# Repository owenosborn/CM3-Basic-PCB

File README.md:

# CM3-Basic-PCB

A basic PCB layout for the Raspberry Pi Compute Module 3 in Eagle.

Uses most of the same parts as the CMIO board.

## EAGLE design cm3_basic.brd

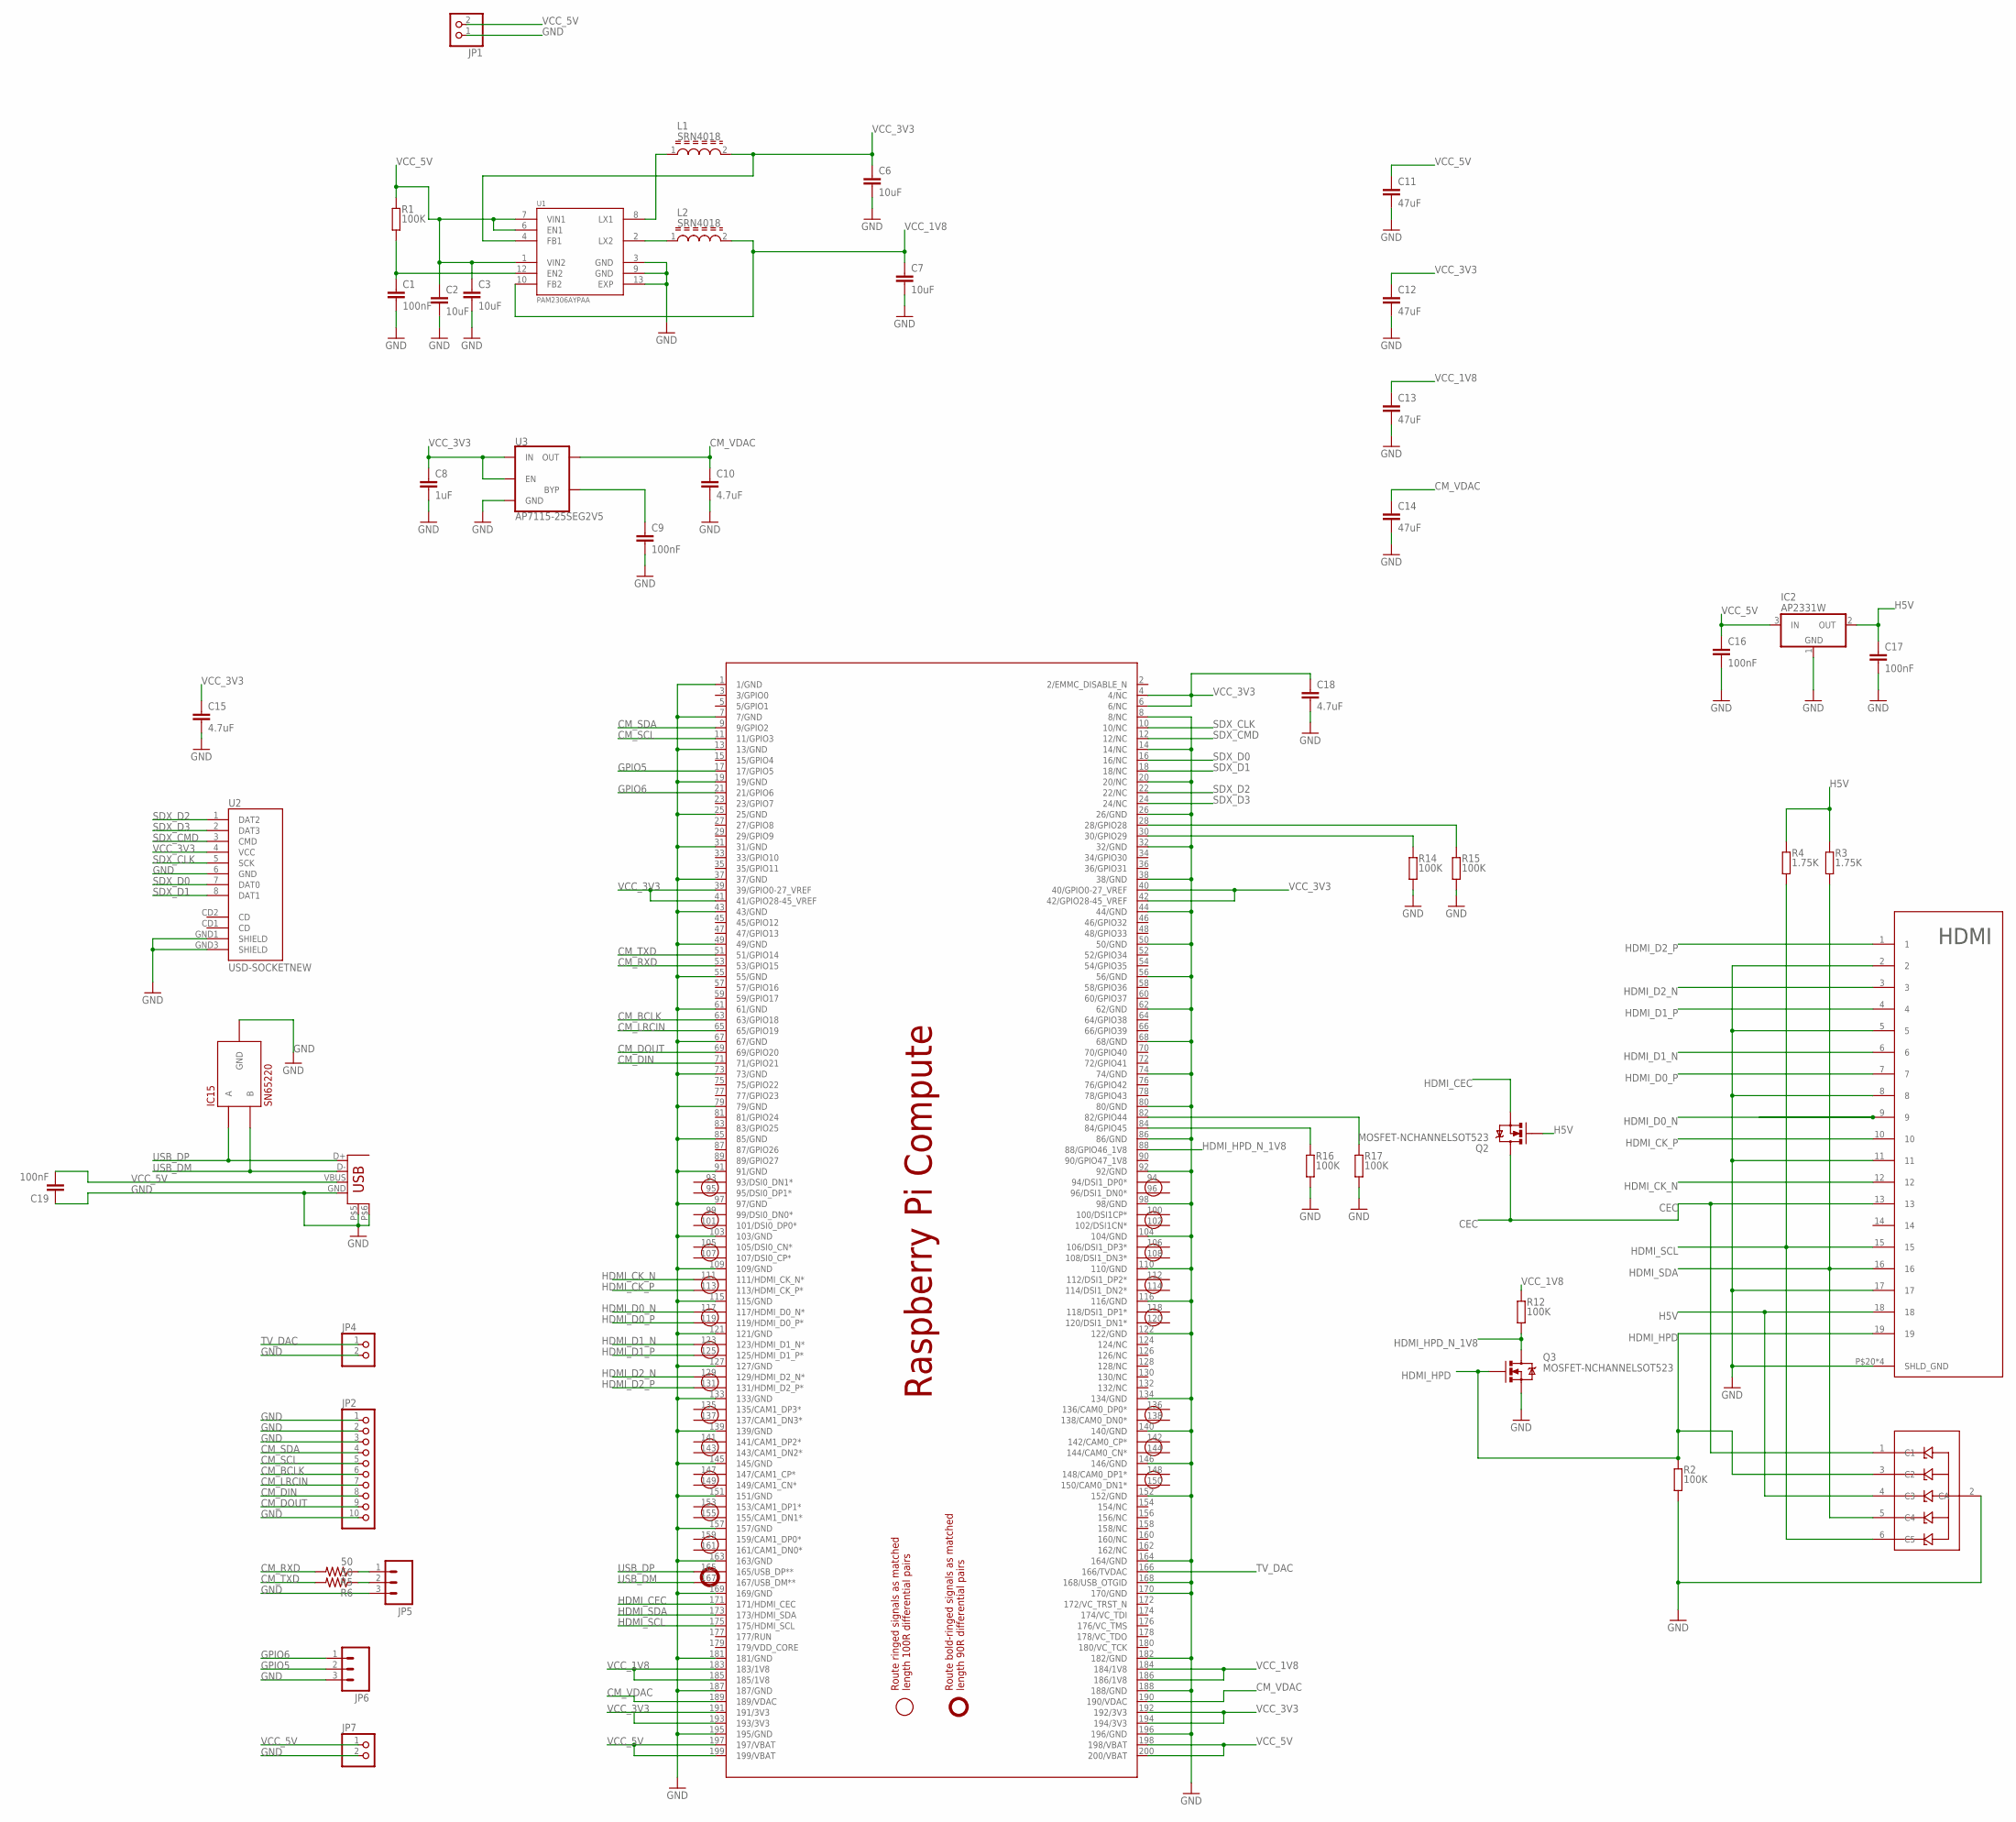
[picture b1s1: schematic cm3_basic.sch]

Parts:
C1, C9, C16, C17: 100nF; C0603
C2, C3, C6, C7: 10uF; C0805
C8: 1uF; C0603
C10, C15: 4.7uF; C0603
C11, C12, C13, C14: 47uF; C3216
C18: 4.7uF; C1608
C19: 100nF; 0603-CAP
IC1: PESD3V3L5UYSOT363; SOT363-INFINION
IC2: AP2331W; SOT23
IC15: SN65220; SOT23-6L
JP1, JP4, JP7: PINHD-1X2; 1X02
JP2: PINHD-1X10; 1X10
JP3: USB-A; USB-A-S-NOSILK-FEMALE
JP5, JP6: M03LOCK_LONGPADS; 1X03_LOCK_LONGPADS
L1, L2: SRN4018; INDP4040X180N
Q2, Q3: MOSFET-NCHANNELSOT523; SOT523
R1, R2, R12, R14, R15, R16, R17: 100K; R0603
R3, R4: 1.75K; R0603
R5, R6: 50; 0603-RES
SODIMM: RPI_COMPUTE
U1: PAM2306AYPAA; SON45P300X300X80-13N
U2: USD-SOCKETNEW; MICRO-SD-SOCKET-PP
U3: AP7115-25SEG2V5; SC70
U4: HDMI

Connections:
CEC: IC1.1 (C1), Q2.3 (D), U4.13
CM_BCLK: JP2.6, SODIMM.63 (63/GPIO18)
CM_DIN: JP2.8, SODIMM.71 (71/GPIO21)
CM_DOUT: JP2.9, SODIMM.69 (69/GPIO20)
CM_LRCIN: JP2.7, SODIMM.65 (65/GPIO19)
CM_RXD: R5.2, SODIMM.53 (53/GPIO15)
CM_SCL: JP2.5, SODIMM.11 (11/GPIO3)
CM_SDA: JP2.4, SODIMM.9 (9/GPIO2)
CM_TXD: R6.2, SODIMM.51 (51/GPIO14)
CM_VDAC: C10.1, C14.1, SODIMM.189 (189/VDAC), SODIMM.190 (190/VDAC), U3.5 (OUT)
GND: C1.2, C2.2, C3.2, C6.2, C7.2, C8.2, C9.2, C10.2, C11.2, C12.2, C13.2, C14.2, C15.2, C16.2, C17.2, C18.2, C19.1, IC1.2 (CA), IC2.1 (GND), IC15.2 (GND), IC15.5 (GND), JP1.1, JP2.1, JP2.2, JP2.3, JP2.10, JP3.GND, JP3.P$5 (SHIELD1), JP3.P$6 (SHIELD2), JP4.2, JP5.3, JP6.3, JP7.2, Q3.2 (S), R2.1, R14.1, R15.1, R16.1, R17.1, SODIMM.1 (1/GND), SODIMM.7 (7/GND), SODIMM.8 (8/NC), SODIMM.13 (13/GND), SODIMM.14 (14/NC), SODIMM.19 (19/GND), SODIMM.20 (20/NC), SODIMM.25 (25/GND), SODIMM.26 (26/GND), SODIMM.31 (31/GND), SODIMM.32 (32/GND), SODIMM.37 (37/GND), SODIMM.38 (38/GND), SODIMM.43 (43/GND), SODIMM.44 (44/GND), SODIMM.49 (49/GND), SODIMM.50 (50/GND), SODIMM.55 (55/GND), SODIMM.56 (56/GND), SODIMM.61 (61/GND), SODIMM.62 (62/GND), SODIMM.67 (67/GND), SODIMM.68 (68/GND), SODIMM.73 (73/GND), SODIMM.74 (74/GND), SODIMM.79 (79/GND), SODIMM.80 (80/GND), SODIMM.85 (85/GND), SODIMM.86 (86/GND), SODIMM.91 (91/GND), SODIMM.92 (92/GND), SODIMM.97 (97/GND), SODIMM.98 (98/GND), SODIMM.103 (103/GND), SODIMM.104 (104/GND), SODIMM.109 (109/GND), SODIMM.110 (110/GND), SODIMM.115 (115/GND), SODIMM.116 (116/GND), SODIMM.121 (121/GND), SODIMM.122 (122/GND), SODIMM.127 (127/GND), SODIMM.133 (133/GND), SODIMM.134 (134/GND), SODIMM.139 (139/GND), SODIMM.140 (140/GND), SODIMM.145 (145/GND), SODIMM.146 (146/GND), SODIMM.151 (151/GND), SODIMM.152 (152/GND), SODIMM.157 (157/GND), SODIMM.163 (163/GND), SODIMM.164 (164/GND), SODIMM.168 (168/USB_OTGID), SODIMM.169 (169/GND), SODIMM.170 (170/GND), SODIMM.181 (181/GND), SODIMM.182 (182/GND), SODIMM.187 (187/GND), SODIMM.188 (188/GND), SODIMM.195 (195/GND), SODIMM.196 (196/GND), U1.3 (GND), U1.9 (GND), U1.13 (EXP), U2.6 (GND), U2.GND1 (SHIELD), U2.GND3 (SHIELD), U3.2 (GND), U4.2, U4.5, U4.8, U4.11, U4.17, U4.P$20 (SHLD_GND), U4.P$21 (SHLD_GND), U4.P$22 (SHLD_GND), U4.P$23 (SHLD_GND)
GPIO5: JP6.2, SODIMM.17 (17/GPIO5)
GPIO6: JP6.1, SODIMM.21 (21/GPIO6)
H5V: C17.1, IC1.4 (C3), IC2.2 (OUT), Q2.1 (G), R3.2, R4.2, U4.18
HDMI_CEC: Q2.2 (S), SODIMM.171 (171/HDMI_CEC)
HDMI_CK_N: SODIMM.111 (111/HDMI_CK_N*), U4.12
HDMI_CK_P: SODIMM.113 (113/HDMI_CK_P*), U4.10
HDMI_D0_N: SODIMM.117 (117/HDMI_D0_N*), U4.9
HDMI_D0_P: SODIMM.119 (119/HDMI_D0_P*), U4.7
HDMI_D1_N: SODIMM.123 (123/HDMI_D1_N*), U4.6
HDMI_D1_P: SODIMM.125 (125/HDMI_D1_P*), U4.4
HDMI_D2_N: SODIMM.129 (129/HDMI_D2_N*), U4.3
HDMI_D2_P: SODIMM.131 (131/HDMI_D2_P*), U4.1
HDMI_HPD: IC1.3 (C2), Q3.1 (G), R2.2, U4.19
HDMI_HPD_N_1V8: Q3.3 (D), R12.1, SODIMM.88 (88/GPIO46_1V8)
HDMI_SCL: IC1.6 (C5), R4.1, SODIMM.175 (175/HDMI_SCL), U4.15
HDMI_SDA: IC1.5 (C4), R3.1, SODIMM.173 (173/HDMI_SDA), U4.16
unnamed: L1.1, U1.8 (LX1)
unnamed: C1.1, R1.1, U1.12 (EN2)
unnamed: JP5.1, R5.1
unnamed: JP5.2, R6.1
unnamed: L2.1, U1.2 (LX2)
unnamed: C9.1, U3.4 (BYP)
unnamed: R16.2, SODIMM.84 (84/GPIO45)
unnamed: R15.2, SODIMM.28 (28/GPIO28)
unnamed: R14.2, SODIMM.30 (30/GPIO29)
unnamed: R17.2, SODIMM.82 (82/GPIO44)
SDX_CLK: SODIMM.10 (10/NC), U2.5 (SCK)
SDX_CMD: SODIMM.12 (12/NC), U2.3 (CMD)
SDX_D0: SODIMM.16 (16/NC), U2.7 (DAT0)
SDX_D1: SODIMM.18 (18/NC), U2.8 (DAT1)
SDX_D2: SODIMM.22 (22/NC), U2.1 (DAT2)
SDX_D3: SODIMM.24 (24/NC), U2.2 (DAT3)
TV_DAC: JP4.1, SODIMM.166 (166/TVDAC)
USB_DM: IC15.4 (B), JP3.D-, SODIMM.167 (167/USB_DM**)
USB_DP: IC15.6 (A), JP3.D+, SODIMM.165 (165/USB_DP**)
VCC_1V8: C7.1, C13.1, L2.2, R12.2, SODIMM.183 (183/1V8), SODIMM.184 (184/1V8), SODIMM.185 (185/1V8), SODIMM.186 (186/1V8), U1.10 (FB2)
VCC_3V3: C6.1, C8.1, C12.1, C15.1, C18.1, L1.2, SODIMM.4 (4/NC), SODIMM.6 (6/NC), SODIMM.39 (39/GPIO0-27_VREF), SODIMM.40 (40/GPIO0-27_VREF), SODIMM.41 (41/GPIO28-45_VREF), SODIMM.42 (42/GPIO28-45_VREF), SODIMM.191 (191/3V3), SODIMM.192 (192/3V3), SODIMM.193 (193/3V3), SODIMM.194 (194/3V3), U1.4 (FB1), U2.4 (VCC), U3.1 (IN), U3.3 (EN)
VCC_5V: C2.1, C3.1, C11.1, C16.1, C19.2, IC2.3 (IN), JP1.2, JP3.VBUS, JP7.1, R1.2, SODIMM.197 (197/VBAT), SODIMM.198 (198/VBAT), SODIMM.199 (199/VBAT), SODIMM.200 (200/VBAT), U1.1 (VIN2), U1.6 (EN1), U1.7 (VIN1)

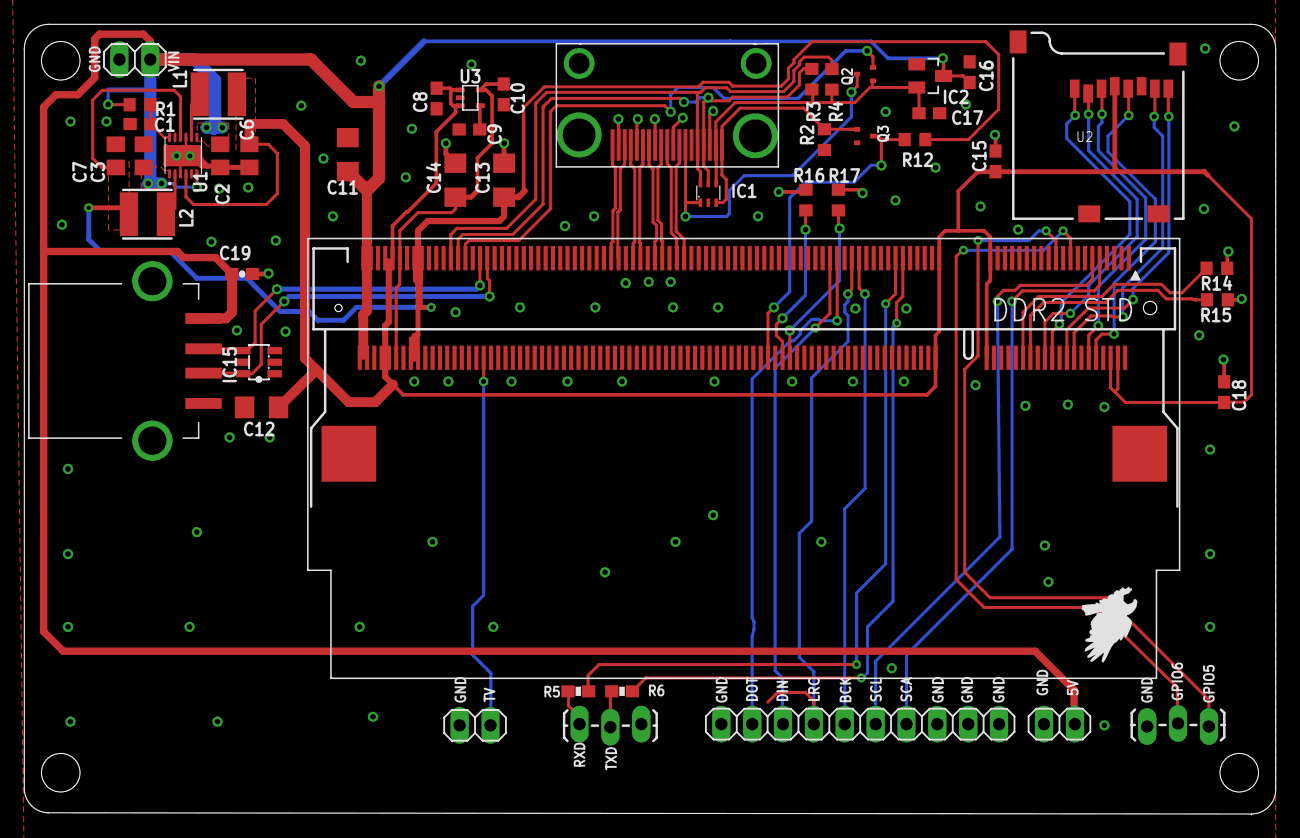
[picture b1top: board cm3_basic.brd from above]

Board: 2 copper layers, 103.0 x 65.0 mm, 47 parts (0 on the bottom side), 49 nets.

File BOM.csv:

Designator,Value,Package,Mounting,Part Number,Supplier,Qty
"C1, C16, C17, C19, C9",".1uF","0603","SMT","478-1239-2-ND","Digikey","5"
"C10, C15, C18","4.7uF","0603","SMT","1276-6684-2-ND	","Digikey","3"
"C11, C12, C13, C14","47uF","1206","SMT","490-8339-2-ND	","Digikey","4"
"C2, C3, C6, C7","10uF","0805","SMT","1276-2893-2-ND	","Digikey","4"
"C8","1uF","0603","SMT","311-1372-2-ND","Digikey","1"
"IC1","","6TSSOP","SMT","1727-3828-1-ND	","Digikey","1"
"IC15","SN65220DBVR","SOT-223-6","SMT","296-9694-1-ND","Digikey","1"
"IC2","","TO-236-3","SMT","AP2331W-7DICT-ND	","Digikey","1"
"JP3","CONN USB","SMT","SMT","609-4413-ND	","Digikey","1"
"L1, L2","4.7UH 1.9A","SMT","SMT","SRN4018-4R7MTR-ND	","Digikey","2"
"Q3, Q2","","SOT523","SMT","DMG1012TQ-7DICT-ND	","Digikey","2"
"R1, R12, R14, R15, R16, R17, R2","100k","603","SMT","P100KGTR-ND","Digikey","7"
"R3, R4","1.8k","0603","SMT","P1.8KGTR-ND","Digikey","2"
"R5, R6","47","0603","SMT","P47GTR-ND	","Digikey","2"
"SODIMM","","","SMT","571-1473149-4","Mouser","1"
"U1","","DFN","SMT","PAM2306AYPKEDICT-ND	","Digikey","1"
"U2","MICROSD","SMT","SMT","3M5607CT-ND	","Digikey","1"
"U3","2.5V","SOT-353","SMT","AP7115-25SEGDICT-ND	","Digikey","1"
"U4","","","PTH","WM14323CT-ND","Digikey","1"

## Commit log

2018-09-14 adding pcb
2018-09-14 added BOM
2018-09-14 add gitignore
2018-09-25 clean up
2018-09-25 adding pcb files
2018-09-25 adding bom
